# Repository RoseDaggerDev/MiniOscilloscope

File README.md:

# MiniOscillscope
This is a little hobby project, taking the EDU09 digital oscilloscope kit from Velleman and redesigning it. I made a through-hole version using the same components as the Velleman kit. And a SMD version using all original parts.

Through-Hole Version: Its been fully tested and works like a charm. Its got a BOM of 87 components and fits on a 50x50mm 2-layer board, manufactured by PCBWay. It took around 3.5 hours to solder after prepping all the components. I underestimated the IC socket size, so things got a bit tight with some parts had to be nudged sideways. I also used the wrong footprint size for the ceramic caps, so they’re a little squished, but everything still worked out in the end!

SMD Version: The SMD version is a compact 25x25mm 4-layer board printed by JLCPCB. It has a BOM of 97 components, including 3 QFNs and four 0402-sized parts, the rest mostly 0603s and SOPs. It took me about 5 hours to solder under a digital microscope, using a hot air rework station and freehanded solder paste. There’s one visible bridge in the upper middle that I’ll clean up later. It’s not really an issue as those pins are already connected by a trace, but it will look cleaner. There’s also some solder blobbing that could be tidied up, but hey, it’s functional (or it will be).

Power rails are looking good, 5V and 3.3V are where they should be, and I’ve confirmed there are no shorts or open circuits on the test points. I haven’t flashed firmware yet because it turns out my old PicKit 3 is too old for the PIC I used, so I’m waiting on a new flasher before I can give it a real test.

Background: The through-hole version was a university project, while the SMD version was my own follow-up challenge. I reverse-engineered the component choices from the original Velleman oscilloscope kit, looking up datasheets and selecting alternatives with similar or improved specs. The original Velleman was around 100x100mm. My through-hole version shrank it to 50x50mm (¼ the size), and the SMD version again cut that down to 25x25mm, or just 1/16 the original footprint. Everything was designed in Proteus 5, since that’s what we use at university.

All in all, I’m really happy with how this turned out. It’s my first full SMD design and soldering job, and despite a few cosmetic hiccups, I think it came together nicely. The through-hole version could have looked neater, but given the part constraints of only using the Velleman kit parts, I’m proud of how compact I got it

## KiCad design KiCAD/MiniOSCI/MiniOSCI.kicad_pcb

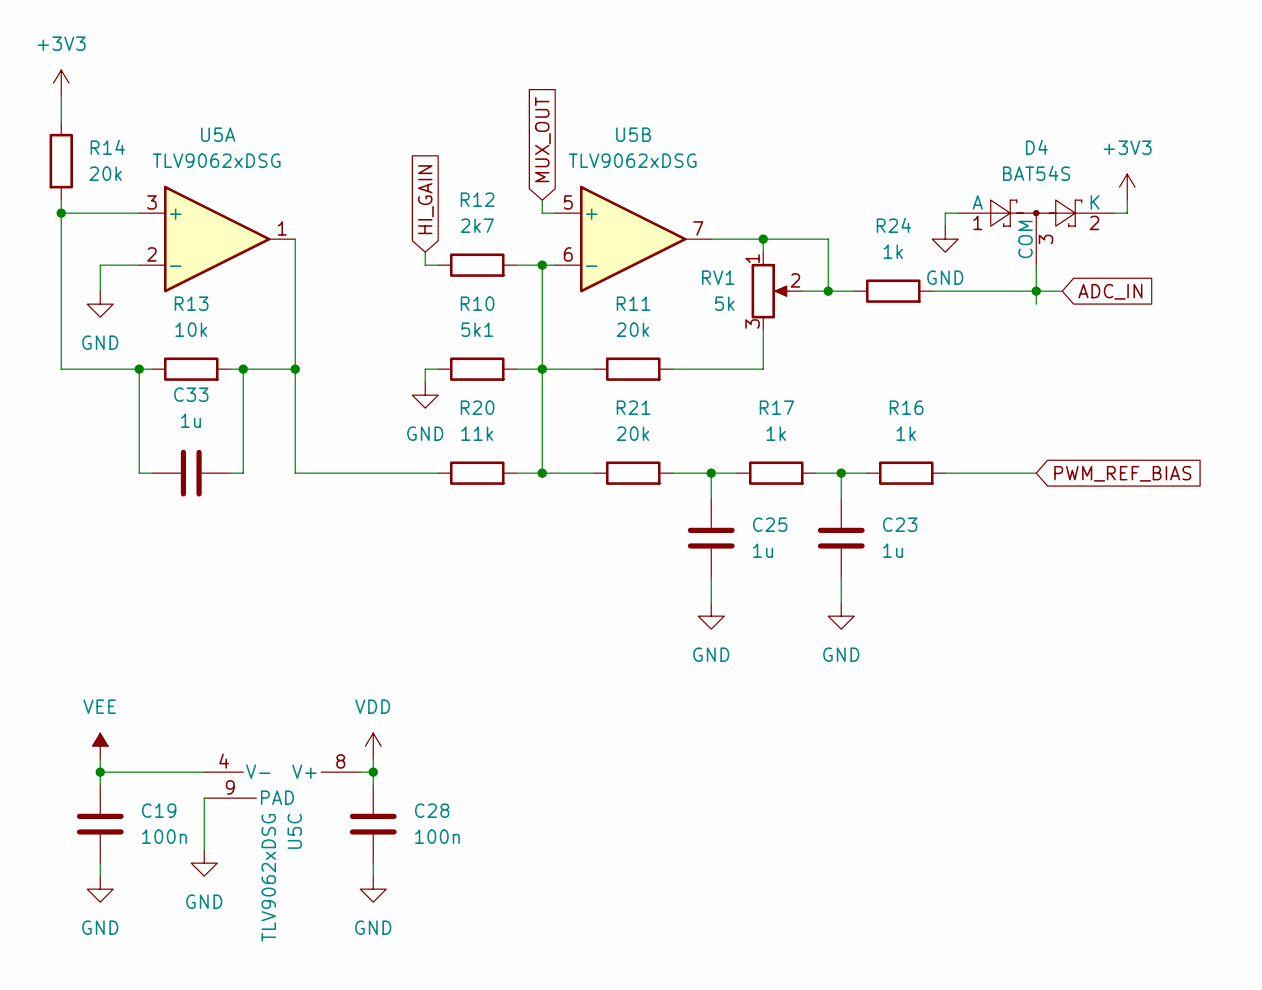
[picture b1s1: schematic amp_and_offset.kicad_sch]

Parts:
C19, C28: 100n; C_0603_1608Metric
C23, C25, C33: 1u; C_0603_1608Metric
D4: BAT54S; SOT-23-3
R10: 5k1; R_0603_1608Metric
R11, R14, R21: 20k; R_0603_1608Metric
R12: 2k7; R_0603_1608Metric
R13: 10k; R_0603_1608Metric
R16, R17, R24: 1k; R_0603_1608Metric
R20: 11k; R_0603_1608Metric
RV1: 5k; Potentiometer_Bourns_TC33X_Vertical
U5: TLV9062xDSG; WSON-8-1EP_2x2mm_P0.5mm_EP0.9x1.6mm

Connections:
+3V3: D4.2 (K), R14.1; also elsewhere on the board
ADC_IN: D4.3 (COM), R24.2; also elsewhere on the board
GND: C19.2, C23.2, C25.2, C28.2, D4.1 (A), R10.1, U5.2 (-), U5.9 (PAD); also elsewhere on the board
HI_GAIN: R12.1; also elsewhere on the board
MUX_OUT: U5.5 (+); also elsewhere on the board
unnamed: C23.1, R16.1, R17.2
unnamed: C25.1, R17.1, R21.2
unnamed: C33.2, R13.2, R20.1, U5.1
unnamed: R11.2, RV1.3
unnamed: R24.1, RV1.1, RV1.2, U5.7
unnamed: C33.1, R13.1, R14.2, U5.3 (+)
unnamed: R10.2, R11.1, R12.2, R20.2, R21.1, U5.6 (-)
PWM_REF_BIAS: R16.2; also elsewhere on the board
VDD: C28.1, U5.8 (V+); also elsewhere on the board
VEE: C19.1, U5.4 (V-); also elsewhere on the board

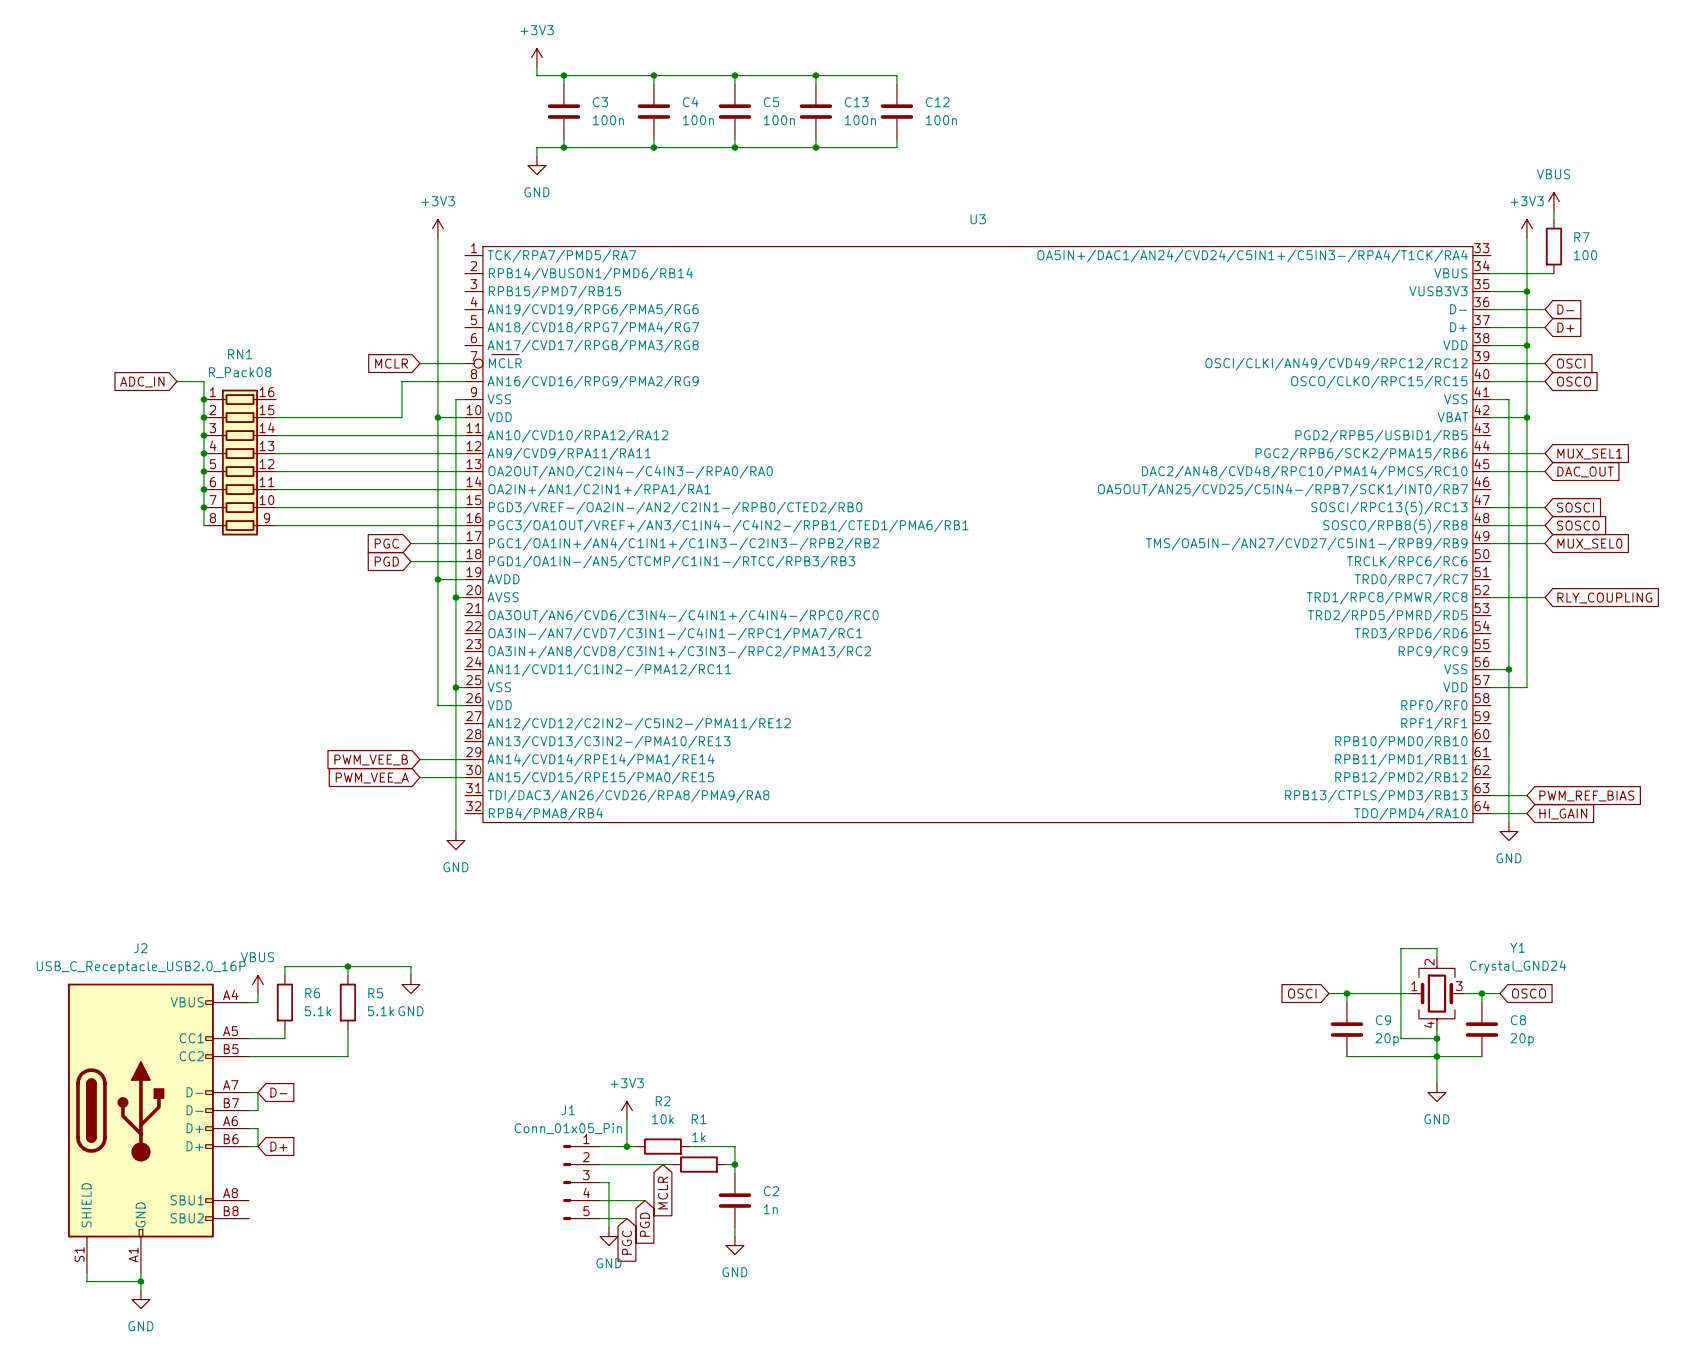
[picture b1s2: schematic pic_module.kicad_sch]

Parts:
C2: 1n; C_0603_1608Metric
C3, C4, C5, C12, C13: 100n; C_0603_1608Metric
C8, C9: 20p; C_0402_1005Metric
J1: Conn_01x05_Pin; PinHeader_1x05_P1.00mm_Vertical
J2: USB_C_Receptacle_USB2.0_16P; USB_C_Receptacle_GCT_USB4105-xx-A_16P_TopMnt_Horizontal
R1: 1k; R_0603_1608Metric
R2: 10k; R_0603_1608Metric
R5, R6: 5.1k; R_0402_1005Metric
R7: 100; R_0402_1005Metric
RN1: R_Pack08; R_Array_Convex_8x0602
U3: VQFN-64-1EP_9x9mm_P0.5mm_EP7.15x7.15mm
Y1: Crystal_GND24; Crystal_SMD_3225-4Pin_3.2x2.5mm

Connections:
+3V3: C3.1, C4.1, C5.1, C12.1, C13.1, J1.1, R2.1, U3.10 (VDD), U3.19 (AVDD), U3.26 (VDD), U3.35 (VUSB3V3), U3.38 (VDD), U3.42 (VBAT), U3.57 (VDD); also elsewhere on the board
ADC_IN: RN1.1 (R1.1), RN1.2 (R2.1), RN1.3 (R3.1), RN1.4 (R4.1), RN1.5 (R5.1), RN1.6 (R6.1), RN1.7 (R7.1), RN1.8 (R8.1); also elsewhere on the board
D+: J2.A6 (D+), J2.B6 (D+), U3.37 (D+)
D-: J2.A7 (D-), J2.B7 (D-), U3.36 (D-)
DAC_OUT: U3.45 (DAC2/AN48/CVD48/RPC10/PMA14/PMCS/RC10); also elsewhere on the board
GND: C2.2, C3.2, C4.2, C5.2, C8.2, C9.2, C12.2, C13.2, J1.3, J2.A1 (GND), J2.A12 (GND), J2.B1 (GND), J2.B12 (GND), J2.S1 (SHIELD), R5.1, R6.1, U3.9 (VSS), U3.20 (AVSS), U3.25 (VSS), U3.41 (VSS), U3.56 (VSS), U3.65, Y1.2, Y1.4; also elsewhere on the board
HI_GAIN: U3.64 (TDO/PMD4/RA10); also elsewhere on the board
MCLR: J1.2, R1.1, U3.7 (MCLR)
MUX_SEL0: U3.49 (TMS/OA5IN-/AN27/CVD27/C5IN1-/RPB9/RB9); also elsewhere on the board
MUX_SEL1: U3.44 (PGC2/RPB6/SCK2/PMA15/RB6); also elsewhere on the board
unnamed: C2.1, R1.2, R2.2
unnamed: J2.A5 (CC1), R6.2
unnamed: J2.B5 (CC2), R5.2
unnamed: RN1.15 (R2.2), U3.8 (AN16/CVD16/RPG9/PMA2/RG9)
unnamed: RN1.14 (R3.2), U3.11 (AN10/CVD10/RPA12/RA12)
unnamed: RN1.13 (R4.2), U3.12 (AN9/CVD9/RPA11/RA11)
unnamed: RN1.12 (R5.2), U3.13 (OA2OUT/ANO/C2IN4-/C4IN3-/RPA0/RA0)
unnamed: RN1.11 (R6.2), U3.14 (OA2IN+/AN1/C2IN1+/RPA1/RA1)
unnamed: RN1.10 (R7.2), U3.15 (PGD3/VREF-/OA2IN-/AN2/C2IN1-/RPB0/CTED2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)
unnamed: RN1.9 (R8.2), U3.16 (PGC3/OA1OUT/VREF+/AN3/C1IN4-/C4IN2-/RPB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)
unnamed: R7.2, U3.34 (VBUS)
OSCI: C9.1, U3.39 (OSCI/CLKI/AN49/CVD49/RPC12/RC12), Y1.1
OSCO: C8.1, U3.40 (OSCO/CLKO/RPC15/RC15), Y1.3
PGC: J1.5, U3.17 (PGC1/OA1IN+/AN4/C1IN1+/C1IN3-/C2IN3-/RP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)
PGD: J1.4, U3.18 (PGD1/OA1IN-/AN5/CTCMP/C1IN1-/RTCC/RPB3/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)
PWM_REF_BIAS: U3.63 (RPB13/CTPLS/PMD3/RB13); also elsewhere on the board
PWM_VEE_A: U3.30 (AN15/CVD15/RPE15/PMA0/RE15); also elsewhere on the board
PWM_VEE_B: U3.29 (AN14/CVD14/RPE14/PMA1/RE14); also elsewhere on the board
RLY_COUPLING: U3.52 (TRD1/RPC8/PMWR/RC8); also elsewhere on the board
SOSCI: U3.47 (SOSCI/RPC13(5)/RC13)
SOSCO: U3.48 (SOSCO/RPB8(5)/RB8)
VBUS: J2.A4 (VBUS), J2.A9 (VBUS), J2.B4 (VBUS), J2.B9 (VBUS), R7.1; also elsewhere on the board

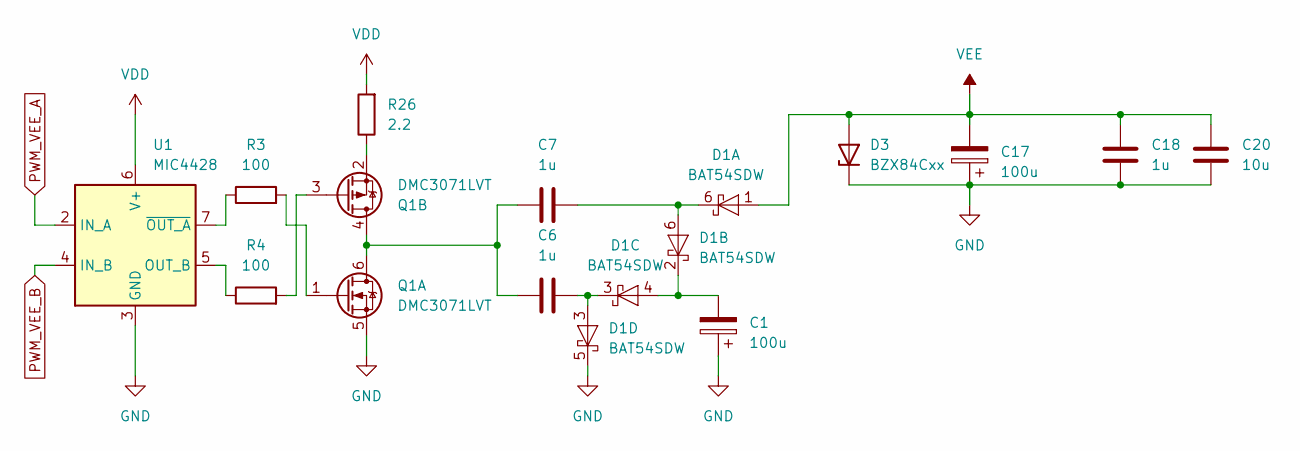
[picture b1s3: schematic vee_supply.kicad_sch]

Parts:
C1, C17: 100u; CP_EIA-3528-12_Kemet-T
C6, C7, C18: 1u; C_0603_1608Metric
C20: 10u; C_0805_2012Metric
D1: BAT54SDW; SOT-363_SC-70-6
D3: BZX84Cxx; SOT-23
Q1: DMC3071LVT; TSOT-23-6
R3, R4: 100; R_0603_1608Metric
R26: 2.2; R_0603_1608Metric
U1: MIC4428; DFN-8-1EP_3x3mm_P0.65mm_EP1.7x2.05mm

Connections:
GND: C1.1, C17.1, C18.1, C20.2, D1.5 (K), D3.3 (K), Q1.5 (S), U1.3 (GND), U1.9; also elsewhere on the board
unnamed: C7.2, D1.6 (K)
unnamed: C1.2, D1.2 (K), D1.4 (A)
unnamed: C6.2, D1.3 (A)
unnamed: C6.1, C7.1, Q1.4 (D), Q1.6 (D)
unnamed: Q1.1 (G), R3.2
unnamed: Q1.3 (G), R4.2
unnamed: Q1.2 (S), R26.1
unnamed: R4.1, U1.5 (OUT_B)
unnamed: R3.1, U1.7 (~OUT_A)
PWM_VEE_A: U1.2 (IN_A); also elsewhere on the board
PWM_VEE_B: U1.4 (IN_B); also elsewhere on the board
VDD: R26.2, U1.6 (V+); also elsewhere on the board
VEE: C17.2, C18.2, C20.1, D1.1 (A), D3.1 (A); also elsewhere on the board

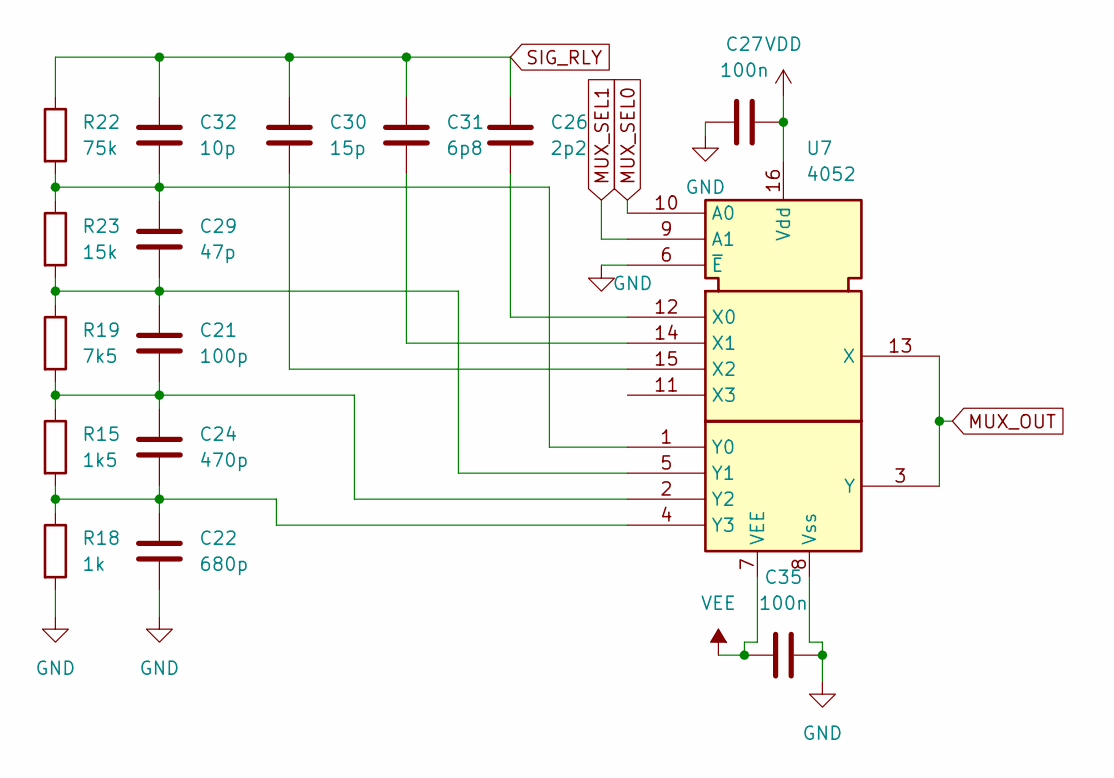
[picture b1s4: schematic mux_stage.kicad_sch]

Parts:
C21: 100p; C_0603_1608Metric
C22: 680p; C_0603_1608Metric
C24: 470p; C_0603_1608Metric
C26: 2p2; C_0603_1608Metric
C27, C35: 100n; C_0603_1608Metric
C29: 47p; C_0603_1608Metric
C30: 15p; C_0603_1608Metric
C31: 6p8; C_0603_1608Metric
C32: 10p; C_0603_1608Metric
R15: 1k5; R_0603_1608Metric
R18: 1k; R_0603_1608Metric
R19: 7k5; R_0603_1608Metric
R22: 75k; R_0603_1608Metric
R23: 15k; R_0603_1608Metric
U7: 4052; DHVQFN-16-1EP_2.5x3.5mm_P0.5mm_EP1x2mm

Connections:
GND: C22.1, C27.1, C35.2, R18.2, U7.6 (~E), U7.8 (Vss), U7.17; also elsewhere on the board
MUX_OUT: U7.3 (Y), U7.13 (X); also elsewhere on the board
MUX_SEL0: U7.10 (A0); also elsewhere on the board
MUX_SEL1: U7.9 (A1); also elsewhere on the board
unnamed: C26.1, U7.12 (X0)
unnamed: C31.1, U7.14 (X1)
unnamed: C30.1, U7.15 (X2)
unnamed: C29.2, C32.1, R22.2, R23.1, U7.1 (Y0)
unnamed: C21.2, C29.1, R19.1, R23.2, U7.5 (Y1)
unnamed: C21.1, C24.2, R15.1, R19.2, U7.2 (Y2)
unnamed: C22.2, C24.1, R15.2, R18.1, U7.4 (Y3)
SIG_RLY: C26.2, C30.2, C31.2, C32.2, R22.1; also elsewhere on the board
VDD: C27.2, U7.16 (Vdd); also elsewhere on the board
VEE: C35.1, U7.7 (VEE); also elsewhere on the board

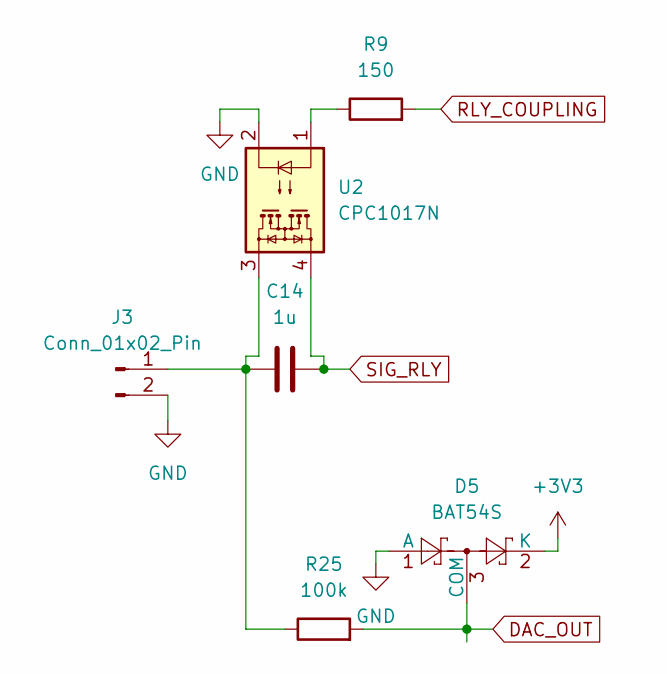
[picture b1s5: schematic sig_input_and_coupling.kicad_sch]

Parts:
C14: 1u; C_0805_2012Metric
D5: BAT54S; SOT-23-3
J3: Conn_01x02_Pin; PinHeader_1x02_P1.27mm_Vertical
R9: 150; R_0603_1608Metric
R25: 100k; R_0603_1608Metric
U2: CPC1017N; SOP-4_3.8x4.1mm_P2.54mm

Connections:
+3V3: D5.2 (K); also elsewhere on the board
DAC_OUT: D5.3 (COM), R25.2; also elsewhere on the board
GND: D5.1 (A), J3.2, U2.2; also elsewhere on the board
unnamed: C14.1, J3.1, R25.1, U2.3
unnamed: R9.1, U2.1
RLY_COUPLING: R9.2; also elsewhere on the board
SIG_RLY: C14.2, U2.4; also elsewhere on the board

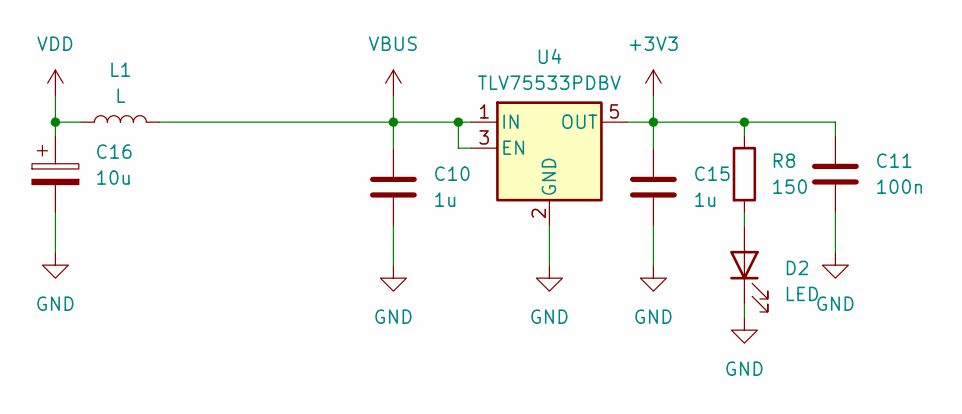
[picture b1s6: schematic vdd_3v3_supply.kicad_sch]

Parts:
C10, C15: 1u; C_0603_1608Metric
C11: 100n; C_0603_1608Metric
C16: 10u; CP_EIA-1608-08_AVX-J
D2: LED; LED_0805_2012Metric
L1: L; L_0603_1608Metric
R8: 150; R_0603_1608Metric
U4: TLV75533PDBV; SOT-23-5

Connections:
+3V3: C11.1, C15.1, R8.1, U4.5 (OUT); also elsewhere on the board
GND: C10.2, C11.2, C15.2, C16.2, D2.1 (K), U4.2 (GND); also elsewhere on the board
unnamed: D2.2 (A), R8.2
VBUS: C10.1, L1.2, U4.1 (IN), U4.3 (EN); also elsewhere on the board
VDD: C16.1, L1.1; also elsewhere on the board

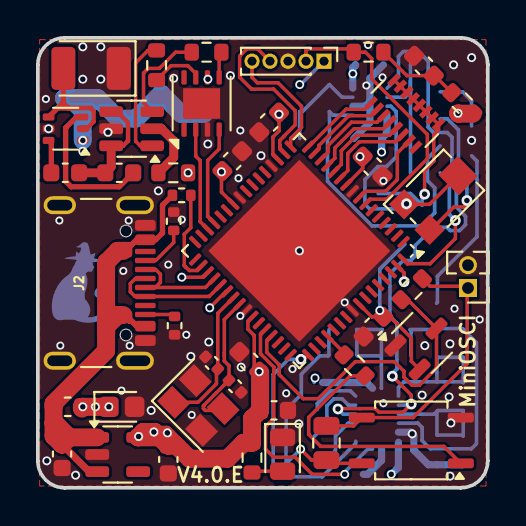
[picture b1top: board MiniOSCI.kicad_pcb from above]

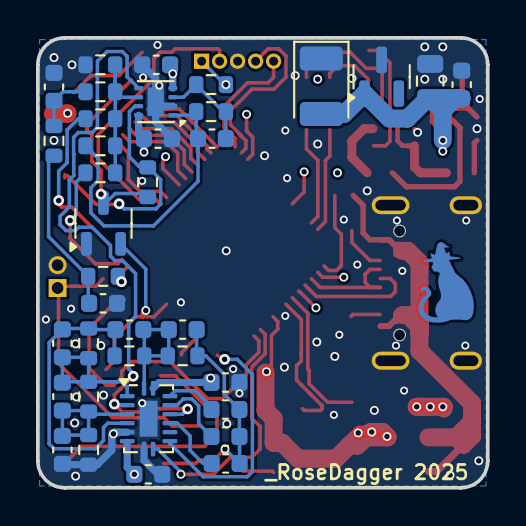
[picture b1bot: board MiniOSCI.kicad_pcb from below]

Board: 4 copper layers, 25.0 x 25.0 mm, 79 parts (37 on the bottom side), 60 nets.

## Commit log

2025-04-24 Project upload
2025-09-09 Added KiCad version
2025-09-09 Added images for kicad version
